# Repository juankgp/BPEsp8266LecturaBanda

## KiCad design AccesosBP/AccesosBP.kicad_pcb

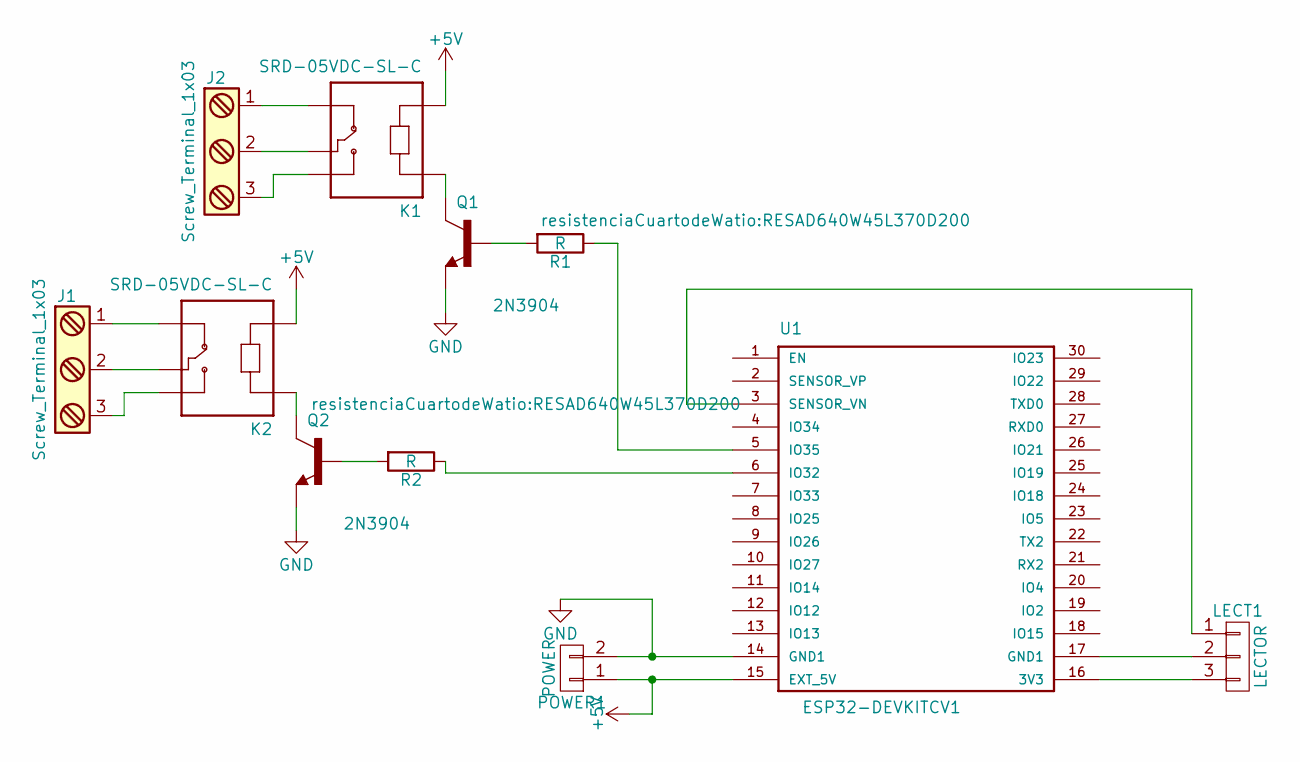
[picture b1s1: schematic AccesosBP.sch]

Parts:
J1, J2: Screw_Terminal_1x03; 691212710003
K1, K2: SRD-05VDC-SL-C; RELAY_SRD-05VDC-SL-C
LECT1: LECTOR; Pin_Header_Straight_1x03
POWER1: POWER; Pin_Header_Straight_1x02
Q1, Q2: 2N3904; TO92127P495H495-3
R1, R2: R; RESAD640W45L370D200
U1: ESP32-DEVKITCV1; ESP32_DEVKITV1-JK

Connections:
+5V: K1.A2, K2.A2, POWER1.1, U1.15 (EXT_5V)
GND: POWER1.2, Q1.1 (E), Q2.1 (E), U1.14 (GND1)
unnamed: J1.1, K2.NC
unnamed: J1.2, K2.COM
unnamed: J1.3, K2.NO
unnamed: J2.1, K1.NC
unnamed: J2.2, K1.COM
unnamed: J2.3, K1.NO
unnamed: K1.A1, Q1.3 (C)
unnamed: K2.A1, Q2.3 (C)
unnamed: LECT1.1, U1.3 (SENSOR_VN)
unnamed: LECT1.2, U1.17 (GND1)
unnamed: LECT1.3, U1.16 (3V3)
unnamed: Q1.2 (B), R1.2
unnamed: Q2.2 (B), R2.2
unnamed: R1.1, U1.5 (IO35)
unnamed: R2.1, U1.6 (IO32)

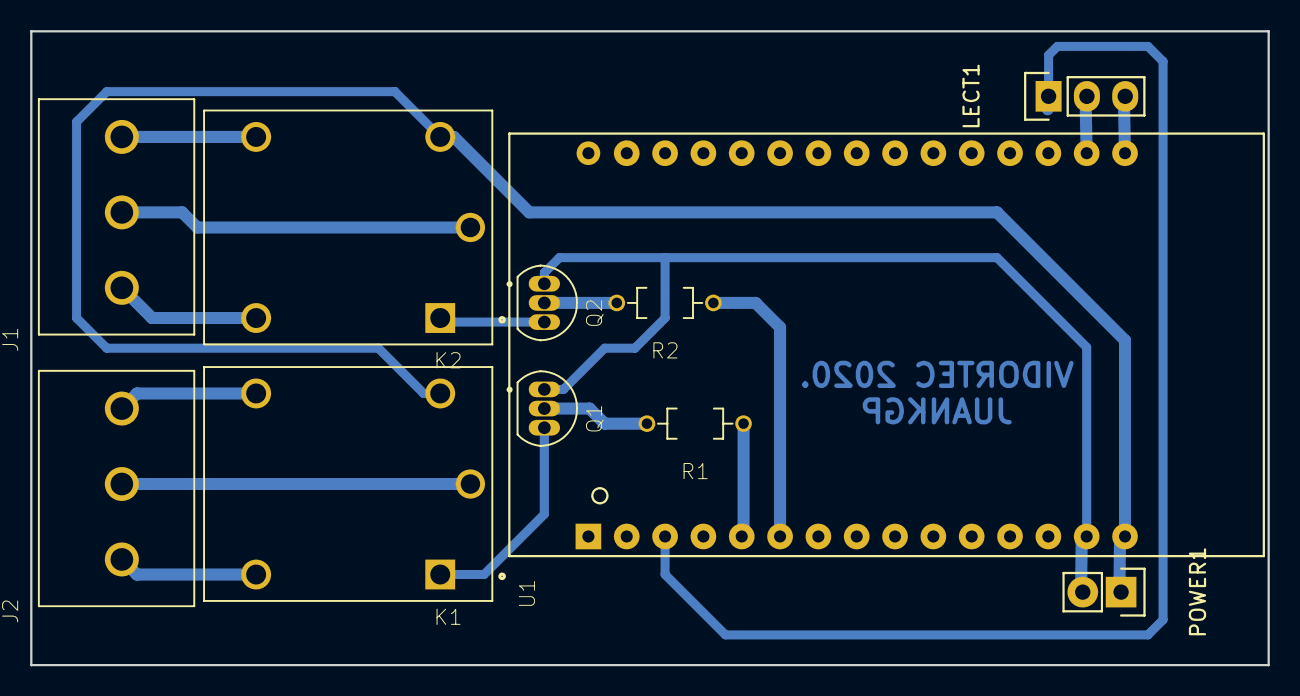
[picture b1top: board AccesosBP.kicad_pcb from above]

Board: 2 copper layers, 82.0 x 42.0 mm, 11 parts (0 on the bottom side), 17 nets.

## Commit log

2020-03-23 Codigo de Esp
2020-03-24 Actualizacion de tiempo de encendido
2020-03-24 New time cj¡hange
2020-03-24 Change time
2020-03-24 Diseños de placas kicad
